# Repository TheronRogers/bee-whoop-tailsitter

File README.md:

# Bee Whoop Tailsitter

Affordable dual-motor, dual-elevon tailsitter platform (Bee). Prototype path: learn custom PCB + printable airframe, then flyable AIO.

## Layout

- `cad/` — Rad CAD / VibeCAD airframe (BeeWhoopTailsitter)
- `electronics/` — Bee Core bring-up board (RP2350 KiCad design)

## Airframe (v0)

| Spec | Value |
|------|--------|
| Span | 120 mm |
| Mean chord | 48 mm (root 52 / tip 44) |
| Area | ~5760 mm² |
| Motors | Y ±30 mm, 40 mm prop discs |
| Elevons | 15 mm chord, 8 mm root gap |
| AIO tray | 32×36×8 mm @ ~33% MAC |
| Battery cue | 1S near LE |
| Servos | 2× micro ~9×12×22 |
| Materials | PLA + Air/LW-PLA; PETG/CF hardpoints |
| AUW / T/W | ~100 g / target 2.0 — verify 0802/1S thrust |

No tilt rotor, swashplate, or collective. Fixed motors + elevons + differential thrust.

## Electronics (Bee Core bring-up)

- RP2350A + QSPI flash + USB-C + SWD
- BMI270 IMU (SPI)
- 1× EFM8BB21 ESC channel, Bluejay **Layout O**, EFM8 on VBAT (1S)
- 1× servo PWM + companion header
- KiCad 9 project under `electronics/bee-core-bringup/bee-core-v01/`
- Schematic ERC clean; **PCB layout not fab-ready** (routing paused for manual finish)
- Bring-up board outline ~80×60 mm; flight target 32×36 mm

See `electronics/bee-core-bringup/` docs (`DESIGN.md`, `ESC-TOPOLOGY-DECISION.md`, `PCB-STATUS.md`).

## Status

**Paused** (see `PAUSED.md`). Notes preserved under `notes/` so the trail survives the pause.

PCB routing still awaits manual / alternate tooling when resumed.

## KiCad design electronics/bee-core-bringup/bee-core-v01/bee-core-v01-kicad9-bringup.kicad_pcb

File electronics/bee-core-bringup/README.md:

# Bee Core — RP2350 bring-up board (v0.1)

Hardware foundation for grafting flight peripherals onto Raspberry Pi’s official
**RP2350A Minimal** KiCad design. Target: JLCPCB PCBA, qty 5, prefer 4-layer.

## Layout

| Path | Contents |
|------|----------|
| `DESIGN.md` | Purpose, block diagram, proof-order, fab posture, scope |
| `BOM-TARGETS.md` | Functional blocks + preferred LCSC candidates |
| `ESC-NOTES.md` | Single-channel whoop ESC topology (cited sources) |
| `NEXT-STEPS.md` | Immediate schematic graft plan |
| `vendor/rp2350-minimal/` | Untouched RPi Minimal KiCad zip extract |
| `vendor/RP2350A_Minimal_USBC/` | JLCPCB/LCSC-mapped fork (funvill) — reference only |
| `kicad/` | Pristine Minimal copy (reference; leave intact) |
| `bee-core-v01/` | **Working KiCad project** + graft sheets; see `SCHEMATIC-NOTES.md` |

## Sources

- Official Minimal: https://datasheets.raspberrypi.com/rp2350/Minimal-KiCAD.zip  
  → `RPI-RP2350A-MINIMAL_R4-S1` (RP2350A QFN-60)
- JLCPCB-mapped fork: https://github.com/funvill/RP2350A_Minimal_USBC
- Hardware design guide: https://datasheets.raspberrypi.com/rp2350/hardware-design-with-rp2350.pdf

## Tooling

| Tool | Version / method |
|------|------------------|
| KiCad | **9.0.2** (`sudo apt-get install -y kicad`, Debian package `9.0.2+dfsg-1`) |
| CLI | `kicad-cli` 9.0.2 (`kicad-cli version`) |
| GUI | `/usr/bin/kicad` (same package; needs display) |

Upstream Minimal sources are **KiCad 10**. Working schematic in `bee-core-v01/` was
downgraded to load in 9.0.2; PCB remains KiCad 10 until a newer KiCad is available.

## Locked v0.1 scope (summary)

RP2350A + QSPI flash + USB-C + SWD + BOOTSEL/RUN + 3V3 from USB; BMI270 or
ICM-42688 SPI IMU; 1× EFM8BB21 Bluejay ESC channel; 1× servo PWM + 5V BEC;
status LED; COMPANION 6-pin header (unpopulated).

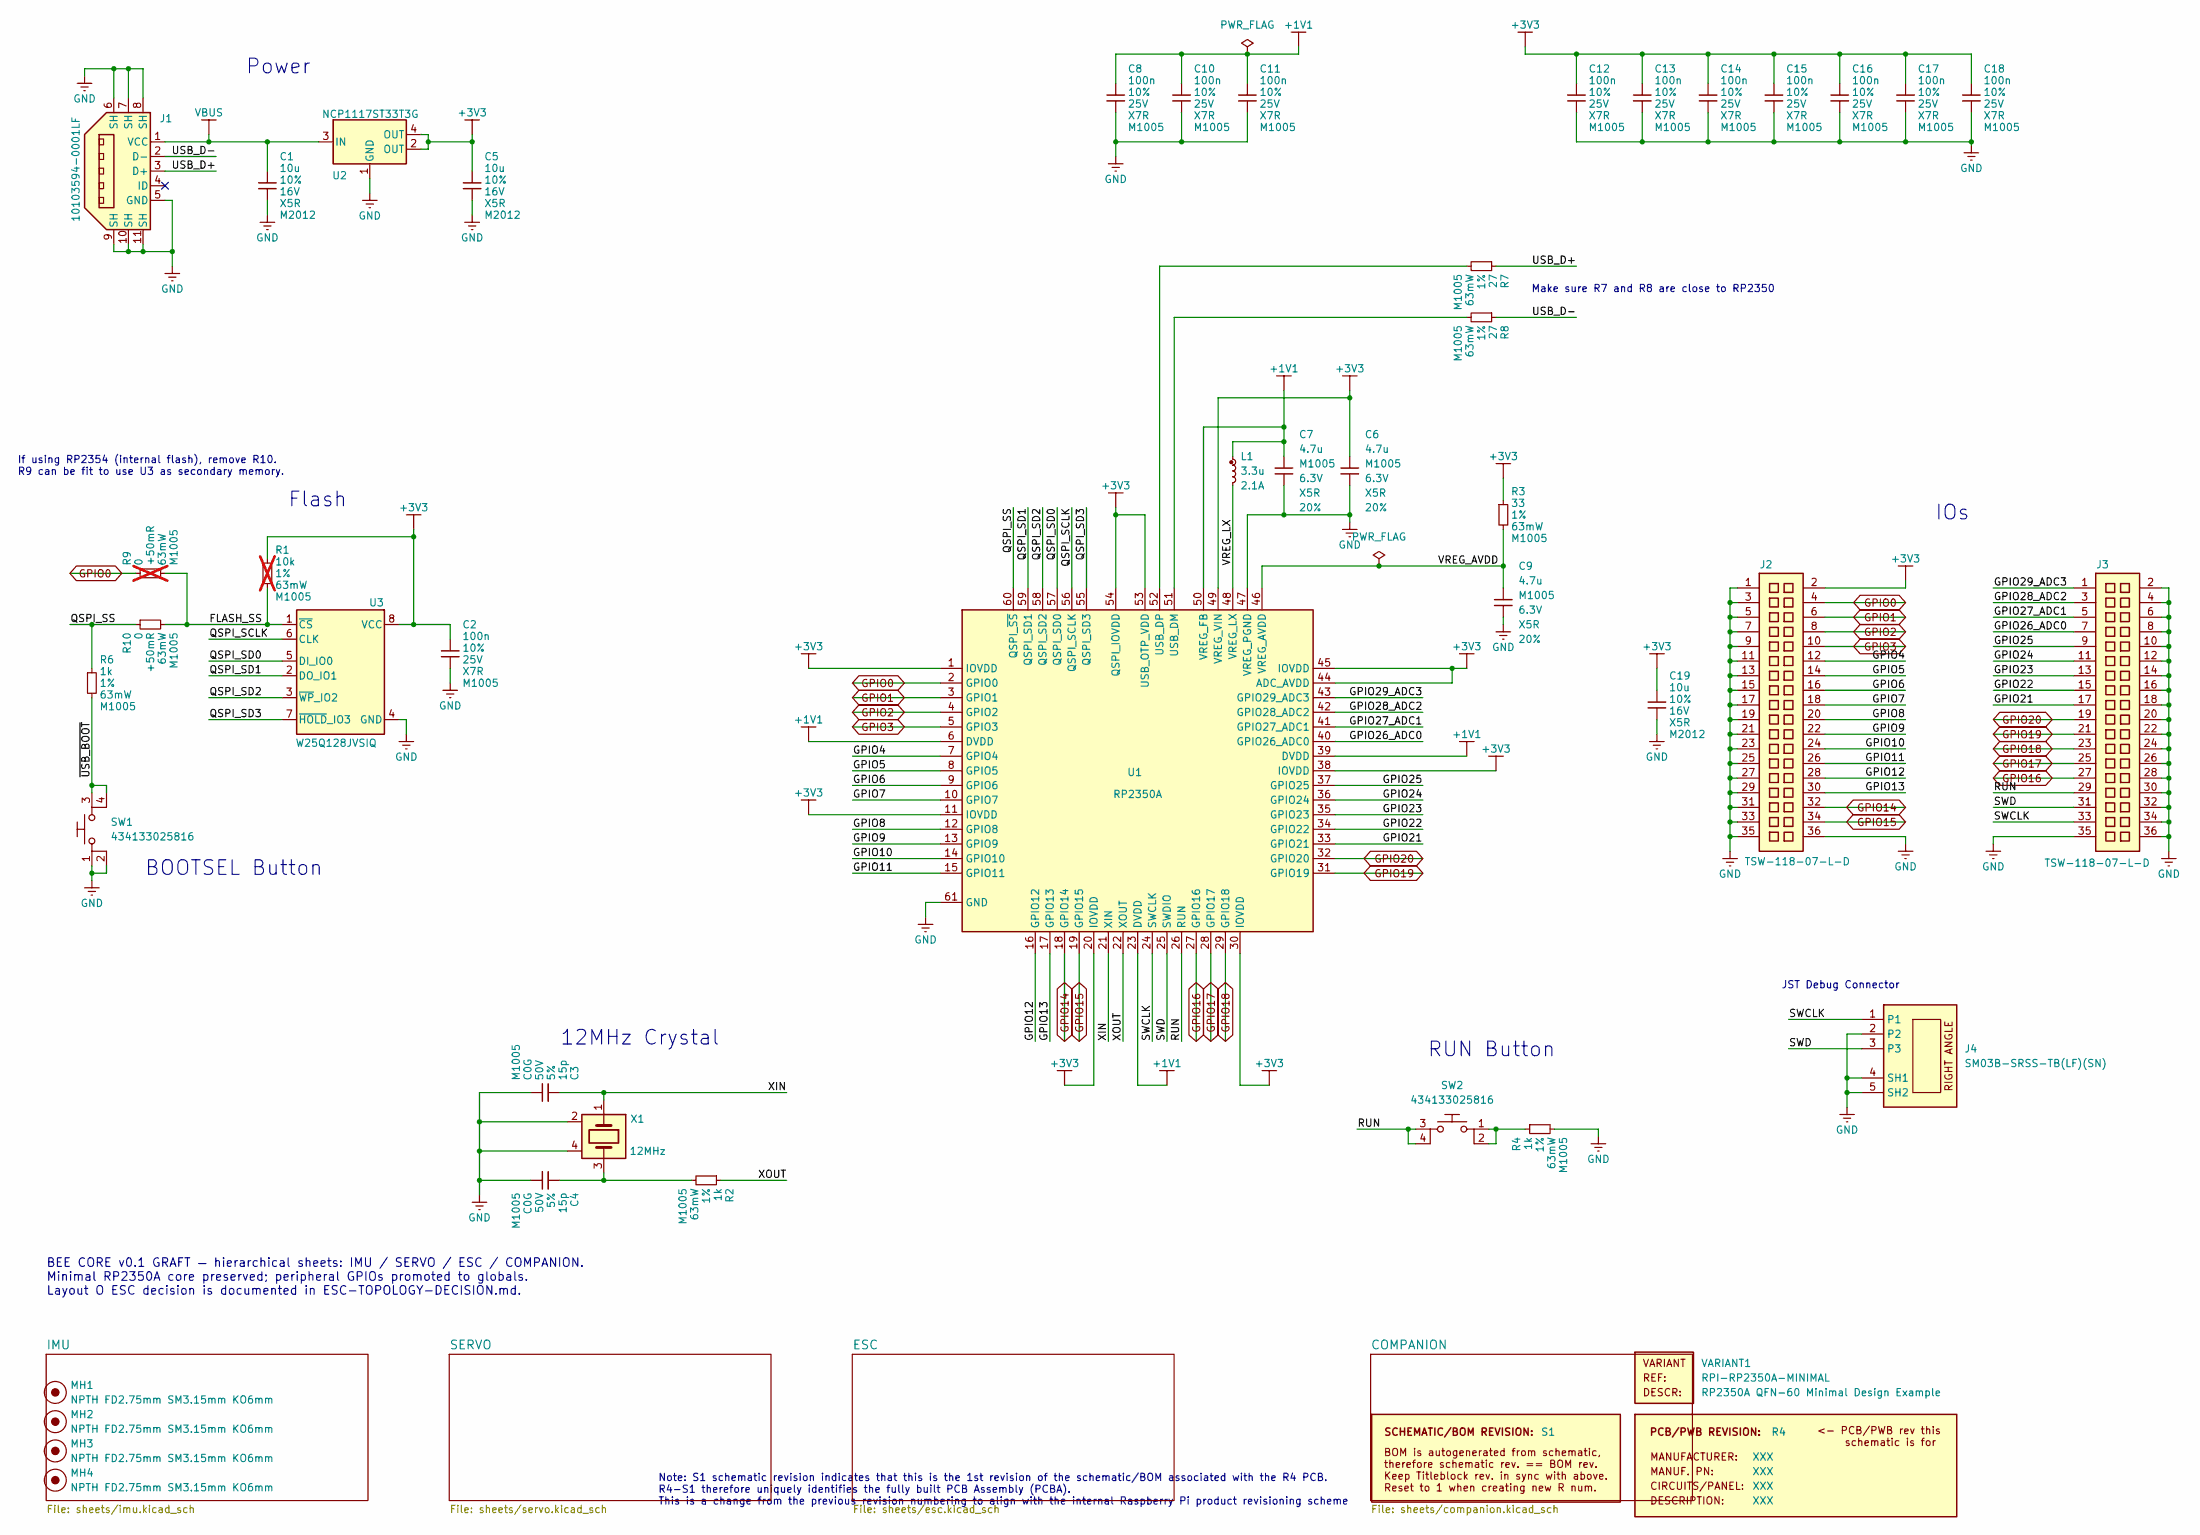
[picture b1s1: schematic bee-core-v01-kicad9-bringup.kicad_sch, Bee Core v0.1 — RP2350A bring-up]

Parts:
C1, C5, C19: 10u; C_0805_2012Metric; voltage 16V; tolerance 10%; part_uid RP-01GYSK-AVBE41
C2, C8, C10, C11, C12, C13, C14, C15, C16, C17, C18: 100n; C_0402_1005Metric; voltage 25V; tolerance 10%; part_uid RP-01BJ9Y-KRGF41
C3, C4: 15p; C_0402_1005Metric; voltage 50V; tolerance 5%; part_uid RP-01C89W-LLY9XV
C6, C7, C9: 4.7u; C_0402_1005Metric; voltage 6.3V; tolerance 20%; part_uid RP-019A1P-0C2GHY
J1: 10103594-0001LF; PinHeader_2x06_P2.54mm_Vertical; part_uid RP-019A1P-1JAX7V
J2, J3: TSW-118-07-L-D; PinHeader_2x18_P2.54mm_Horizontal; part_uid RP-01JWH2-G371Y4
J4: SM03B-SRSS-TB(LF)(SN); PinHeader_1x05_P2.54mm_Vertical; part_uid RP-01EKJ1-8V9SV1
L1: 3.3u; L_Cenker_CKCS201610; tolerance 20%; part_uid RP-01GY5D-2VC7WP
MH1, MH2, MH3, MH4: NPTH FD2.75mm SM3.15mm KO6mm; MountingHole_2.7mm_M2.5; part_uid RP-01HF5R-LCTEJS
PCB1: R4; manufacturer_pn XXX
R1: 10k; R_0402_1005Metric; tolerance 1%; voltage 50V; part_uid RP-019A1P-53DHSX; not fitted
R2, R4, R6: 1k; R_0402_1005Metric; tolerance 1%; voltage 50V; part_uid RP-019A1P-4Z6ZWY
R3: 33; R_0402_1005Metric; tolerance 1%; voltage 50V; part_uid RP-019A1P-58PW9L
R7, R8: 27; R_0402_1005Metric; tolerance 1%; voltage 50V; part_uid RP-01C89V-LTEYC4
R9: 0; R_0402_1005Metric; tolerance +50mR; voltage 50V; part_uid RP-019A1P-4Y4V63; not fitted
R10: 0; R_0402_1005Metric; tolerance +50mR; voltage 50V; part_uid RP-019A1P-4Y4V63
SBREV1: S1
SW1, SW2: 434133025816; PinHeader_1x04_P2.54mm_Vertical; part_uid RP-01H0MT-6E9H8F
U1: RP2350A; QFN-60-1EP_7x7mm_P0.4mm_EP3.4x3.4mm_ThermalVias; part_uid RP-01HA9H-9K5E8T
U2: NCP1117ST33T3G; SOIC-8_3.9x4.9mm_P1.27mm; voltage 3.3V; part_uid RP-01JWD9-7JRX6J
U3: W25Q128JVSIQ; SOIC-8_3.9x4.9mm_P1.27mm; voltage 2.7-3.6V; part_uid RP-01JWD4-F1H4N9
VARIANT1: RPI-RP2350A-MINIMAL
X1: 12MHz; Crystal_SMD_3225-4Pin_3.2x2.5mm; tolerance 30ppm; part_uid RP-01G8X7-GS352B

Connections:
+1V1: C7.1, C8.1, C10.1, C11.1, L1.1, U1.6 (DVDD), U1.23 (DVDD), U1.39 (DVDD), U1.50 (VREG_FB)
+3V3: C2.1, C5.1, C6.1, C12.1, C13.1, C14.1, C15.1, C16.1, C17.1, C18.1, C19.1, J2.2, R1.1, R3.1, U1.1 (IOVDD), U1.11 (IOVDD), U1.20 (IOVDD), U1.30 (IOVDD), U1.38 (IOVDD), U1.44 (ADC_AVDD), U1.45 (IOVDD), U1.49 (VREG_VIN), U1.53 (USB_OTP_VDD), U1.54 (QSPI_IOVDD), U2.2 (OUT), U2.4 (OUT), U3.8 (VCC); also elsewhere on the board
/FLASH_SS: R1.2, R9.2, R10.2, U3.1 (~CS)
/GPIO4: J2.12, U1.7 (GPIO4)
/GPIO5: J2.14, U1.8 (GPIO5)
/GPIO6: J2.16, U1.9 (GPIO6)
/GPIO7: J2.18, U1.10 (GPIO7)
/GPIO8: J2.20, U1.12 (GPIO8)
/GPIO9: J2.22, U1.13 (GPIO9)
/GPIO10: J2.24, U1.14 (GPIO10)
/GPIO11: J2.26, U1.15 (GPIO11)
/GPIO12: J2.28, U1.16 (GPIO12)
/GPIO13: J2.30, U1.17 (GPIO13)
/GPIO21: J3.17, U1.33 (GPIO21)
/GPIO22: J3.15, U1.34 (GPIO22)
/GPIO23: J3.13, U1.35 (GPIO23)
/GPIO24: J3.11, U1.36 (GPIO24)
/GPIO25: J3.9, U1.37 (GPIO25)
/GPIO26_ADC0: J3.7, U1.40 (GPIO26_ADC0)
/GPIO27_ADC1: J3.5, U1.41 (GPIO27_ADC1)
/GPIO28_ADC2: J3.3, U1.42 (GPIO28_ADC2)
/GPIO29_ADC3: J3.1, U1.43 (GPIO29_ADC3)
/QSPI_SCLK: U1.56 (QSPI_SCLK), U3.6 (CLK)
/QSPI_SD0: U1.57 (QSPI_SD0), U3.5 (DI_IO0)
/QSPI_SD1: U1.59 (QSPI_SD1), U3.2 (DO_IO1)
/QSPI_SD2: U1.58 (QSPI_SD2), U3.3 (~WP_IO2)
/QSPI_SD3: U1.55 (QSPI_SD3), U3.7 (~HOLD_IO3)
/QSPI_SS: R6.1, R10.1, U1.60 (QSPI_~SS)
/RUN: J3.29, SW2.3, SW2.4, U1.26 (RUN)
/SWCLK: J3.33, J4.1, U1.24 (SWCLK)
/SWD: J3.31, J4.3, U1.25 (SWDIO)
/USB_D+: J1.3 (D+), R7.1
/USB_D-: J1.2 (D-), R8.1
/VREG_AVDD: C9.1, R3.2, U1.46 (VREG_AVDD)
/VREG_LX: L1.2, U1.48 (VREG_LX)
/XIN: C3.1, U1.21 (XIN), X1.1
/XOUT: R2.1, U1.22 (XOUT)
/~USB_BOOT: R6.2, SW1.3, SW1.4
GND: C1.2, C2.2, C3.2, C4.2, C5.2, C6.2, C7.2, C8.2, C9.2, C10.2, C11.2, C12.2, C13.2, C14.2, C15.2, C16.2, C17.2, C18.2, C19.2, J1.5 (GND), J1.6 (SH), J1.7 (SH), J1.8 (SH), J1.9 (SH), J1.10 (SH), J1.11 (SH), J2.1, J2.3, J2.5, J2.7, J2.9, J2.11, J2.13, J2.15, J2.17, J2.19, J2.21, J2.23, J2.25, J2.27, J2.29, J2.31, J2.33, J2.35, J2.36, J3.2, J3.4, J3.6, J3.8, J3.10, J3.12, J3.14, J3.16, J3.18, J3.20, J3.22, J3.24, J3.26, J3.28, J3.30, J3.32, J3.34, J3.35, J3.36, J4.2, J4.4 (SH1), J4.5 (SH2), R4.2, SW1.1, SW1.2, U1.47 (VREG_PGND), U1.61 (GND), U2.1 (GND), U3.4 (GND), X1.2, X1.4; also elsewhere on the board
GPIO0: J2.4, R9.1, U1.2 (GPIO0); also elsewhere on the board
GPIO1: J2.6, U1.3 (GPIO1)
GPIO2: J2.8, U1.4 (GPIO2); also elsewhere on the board
GPIO3: J2.10, U1.5 (GPIO3); also elsewhere on the board
GPIO14: J2.32, U1.18 (GPIO14); also elsewhere on the board
GPIO15: J2.34, U1.19 (GPIO15); also elsewhere on the board
GPIO16: J3.27, U1.27 (GPIO16); also elsewhere on the board
GPIO17: J3.25, U1.28 (GPIO17); also elsewhere on the board
GPIO18: J3.23, U1.29 (GPIO18); also elsewhere on the board
GPIO19: J3.21, U1.31 (GPIO19); also elsewhere on the board
GPIO20: J3.19, U1.32 (GPIO20); also elsewhere on the board
unnamed: C4.1, R2.2, X1.3
unnamed: R4.1, SW2.1, SW2.2
unnamed: R8.2, U1.51 (USB_DM)
unnamed: R7.2, U1.52 (USB_DP)
VBUS: C1.1, J1.1 (VCC), U2.3 (IN)

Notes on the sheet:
JST Debug Connector
IOs
RUN Button
BOOTSEL Button
If using RP2354 (internal flash), remove R10. R9 can be fit to use U3 as secondary memory.
BEE CORE v0.1 GRAFT — hierarchical sheets: IMU / SERVO / ESC / COMPANION. Minimal RP2350A core preserved; peripheral GPIOs promoted to globals. Layout O ESC decision is documented in ESC-TOPOLOGY-DECISION.md.
Flash
Note: S1 schematic revision indicates that this is the 1st revision of the schematic/BOM associated with the R4 PCB. R4-S1 therefore uniquely identifies the fully built PCB Assembly (PCBA). This is a change from the previous revision numbering to align with the internal Raspberry Pi product revisio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
Make sure R7 and R8 are close to RP2350
12MHz Crystal
Power

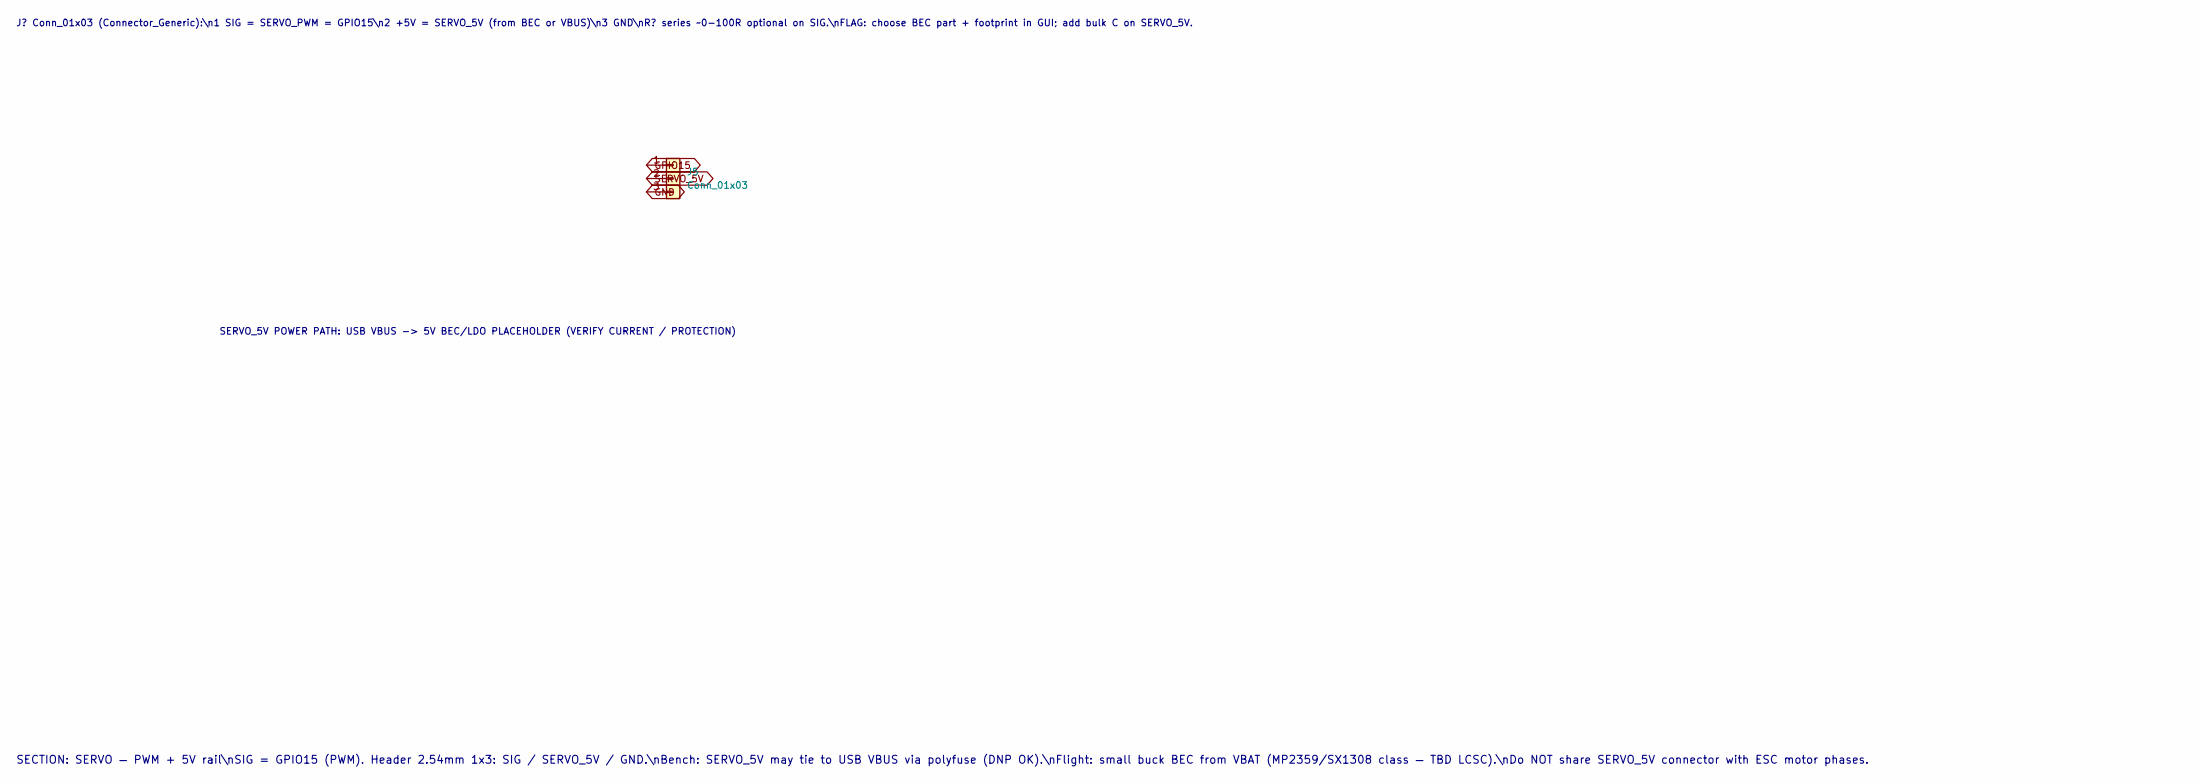
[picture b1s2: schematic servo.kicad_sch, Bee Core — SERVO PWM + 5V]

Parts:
J5: Conn_01x03; PinHeader_1x03_P2.54mm_Vertical

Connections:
GND: J5.3; also elsewhere on the board
GPIO15: J5.1; also elsewhere on the board
SERVO_5V: J5.2

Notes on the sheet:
J? Conn_01x03 (Connector_Generic):\n1 SIG = SERVO_PWM = GPIO15\n2 +5V = SERVO_5V (from BEC or VBUS)\n3 GND\nR? series ~0-100R optional on SIG.\nFLAG: choose BEC part + footprint in GUI; add bulk C on SERVO_5V.
SERVO_5V POWER PATH: USB VBUS -> 5V BEC/LDO PLACEHOLDER (VERIFY CURRENT / PROTECTION)
SECTION: SERVO — PWM + 5V rail\nSIG = GPIO15 (PWM). Header 2.54mm 1x3: SIG / SERVO_5V / GND.\nBench: SERVO_5V may tie to USB VBUS via polyfuse (DNP OK).\nFlight: small buck BEC from VBAT (MP2359/SX1308 class — TBD LCSC).\nDo NOT share SERVO_5V connector with ESC motor phases.

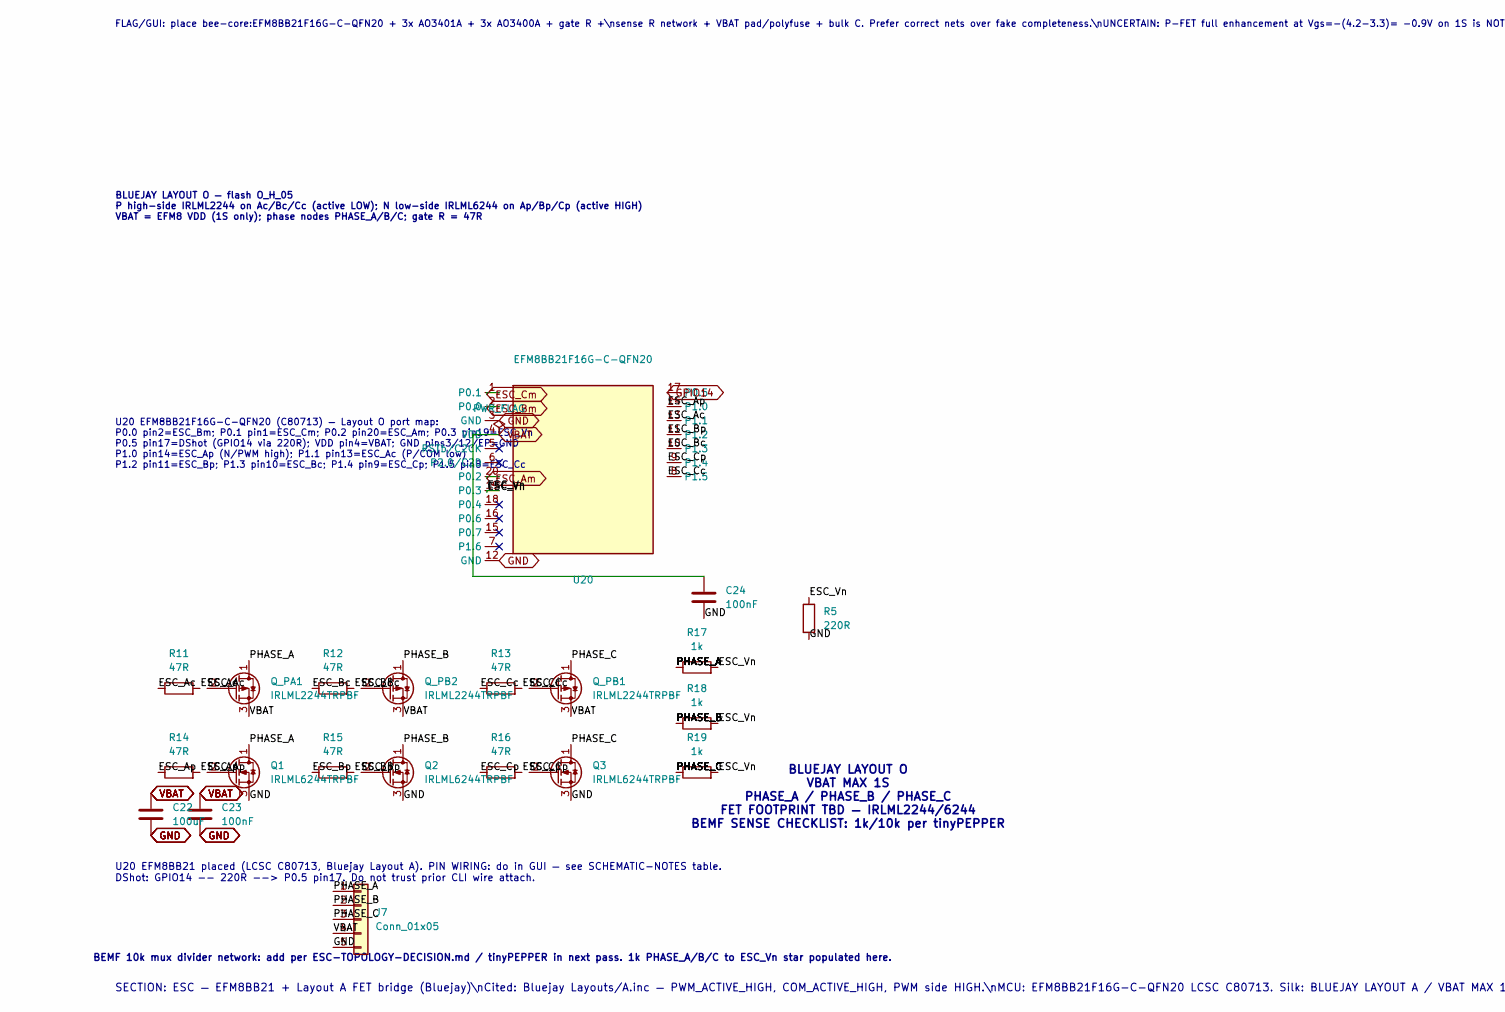
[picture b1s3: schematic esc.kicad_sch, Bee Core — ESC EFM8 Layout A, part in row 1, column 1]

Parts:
C22: 100uF; C_0805_2012Metric_Pad1.18x1.45mm_HandSolder
C23, C24: 100nF; C_0402_1005Metric
J7: Conn_01x05; PinHeader_1x05_P2.54mm_Vertical
Q1, Q2, Q3: IRLML6244TRPBF; SOT-23-3
Q_PA1: IRLML2244TRPBF; SOT-23-3
Q_PB1, Q_PB2: IRLML2244TRPBF; SOT-23-3
R5: 220R; R_0402_1005Metric_Pad0.72x0.64mm_HandSolder
R11, R12, R13, R14, R15, R16: 47R; R_0402_1005Metric_Pad0.72x0.64mm_HandSolder
R17, R18, R19: 1k; R_0402_1005Metric_Pad0.72x0.64mm_HandSolder
U20: EFM8BB21F16G-C-QFN20; SiliconLabs_QFN-20-1EP_3x3mm_P0.5mm_EP1.8x1.8mm; LCSC C80713

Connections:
/ESC/ESC_Ac: Q_PA1.2 (G), R11.1, R11.2, U20.13 (P1.1)
/ESC/ESC_Ap: Q1.2 (G), R14.1, R14.2, U20.14 (P1.0)
/ESC/ESC_Bc: Q_PB2.2 (G), R12.1, R12.2, U20.10 (P1.3)
/ESC/ESC_Bp: Q2.2 (G), R15.1, R15.2, U20.11 (P1.2)
/ESC/ESC_Cc: Q_PB1.2 (G), R13.1, R13.2, U20.8 (P1.5)
/ESC/ESC_Cp: Q3.2 (G), R16.1, R16.2, U20.9 (P1.4)
/ESC/ESC_Vn: R5.1, R17.2, R18.2, R19.2, U20.19 (P0.3)
/ESC/PHASE_A: J7.1, Q1.1 (D), Q_PA1.1 (D), R17.1
/ESC/PHASE_B: J7.2, Q2.1 (D), Q_PB2.1 (D), R18.1
/ESC/PHASE_C: J7.3, Q3.1 (D), Q_PB1.1 (D), R19.1
ESC_Am: U20.20 (P0.2)
ESC_Bm: U20.2 (P0.0)
ESC_Cm: U20.1 (P0.1)
GND: C22.2, C23.2, C24.2, J7.5, Q1.3 (S), Q2.3 (S), Q3.3 (S), R5.2, U20.3 (GND), U20.12 (GND); also elsewhere on the board
GPIO14: U20.17 (P0.5); also elsewhere on the board
VBAT: C22.1, C23.1, C24.1, J7.4, Q_PA1.3 (S), Q_PB1.3 (S), Q_PB2.3 (S), U20.4 (VDD)

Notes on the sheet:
U20 EFM8BB21 placed (LCSC C80713, Bluejay Layout A). PIN WIRING: do in GUI — see SCHEMATIC-NOTES table. DShot: GPIO14 -- 220R --> P0.5 pin17. Do not trust prior CLI wire attach.
BLUEJAY LAYOUT O VBAT MAX 1S PHASE_A / PHASE_B / PHASE_C FET FOOTPRINT TBD — IRLML2244/6244 BEMF SENSE CHECKLIST: 1k/10k per tinyPEPPER
BLUEJAY LAYOUT O — flash O_H_05 P high-side IRLML2244 on Ac/Bc/Cc (active LOW); N low-side IRLML6244 on Ap/Bp/Cp (active HIGH) VBAT = EFM8 VDD (1S only); phase nodes PHASE_A/B/C; gate R = 47R
U20 EFM8BB21F16G-C-QFN20 (C80713) — Layout O port map: P0.0 pin2=ESC_Bm; P0.1 pin1=ESC_Cm; P0.2 pin20=ESC_Am; P0.3 pin19=ESC_Vn P0.5 pin17=DShot (GPIO14 via 220R); VDD pin4=VBAT; GND pins3/12/EP=GND P1.0 pin14=ESC_Ap (N/PWM high); P1.1 pin13=ESC_Ac (P/COM low) P1.2 pin11=ESC_Bp; P1.3 pin10=ESC_Bc; 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
FLAG/GUI: place bee-core:EFM8BB21F16G-C-QFN20 + 3x AO3401A + 3x AO3400A + gate R +\nsense R network + VBAT pad/polyfuse + bulk C. Prefer correct nets over fake completeness.\nUNCERTAIN: P-FET full enhancement at Vgs=-(4.2-3.3)= -0.9V on 1S is NOT enough —\nwhoop designs often gate P-FETs from VBAT-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
BEMF 10k mux divider network: add per ESC-TOPOLOGY-DECISION.md / tinyPEPPER in next pass. 1k PHASE_A/B/C to ESC_Vn star populated here.
SECTION: ESC — EFM8BB21 + Layout A FET bridge (Bluejay)\nCited: Bluejay Layouts/A.inc — PWM_ACTIVE_HIGH, COM_ACTIVE_HIGH, PWM side HIGH.\nMCU: EFM8BB21F16G-C-QFN20 LCSC C80713. Silk: BLUEJAY LAYOUT A / VBAT MAX 1S.\nDShot: GPIO14 -- Rseries 100-330R --> EFM8 P0.5 (pin 17).\n1S direct-drive P+N whoo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

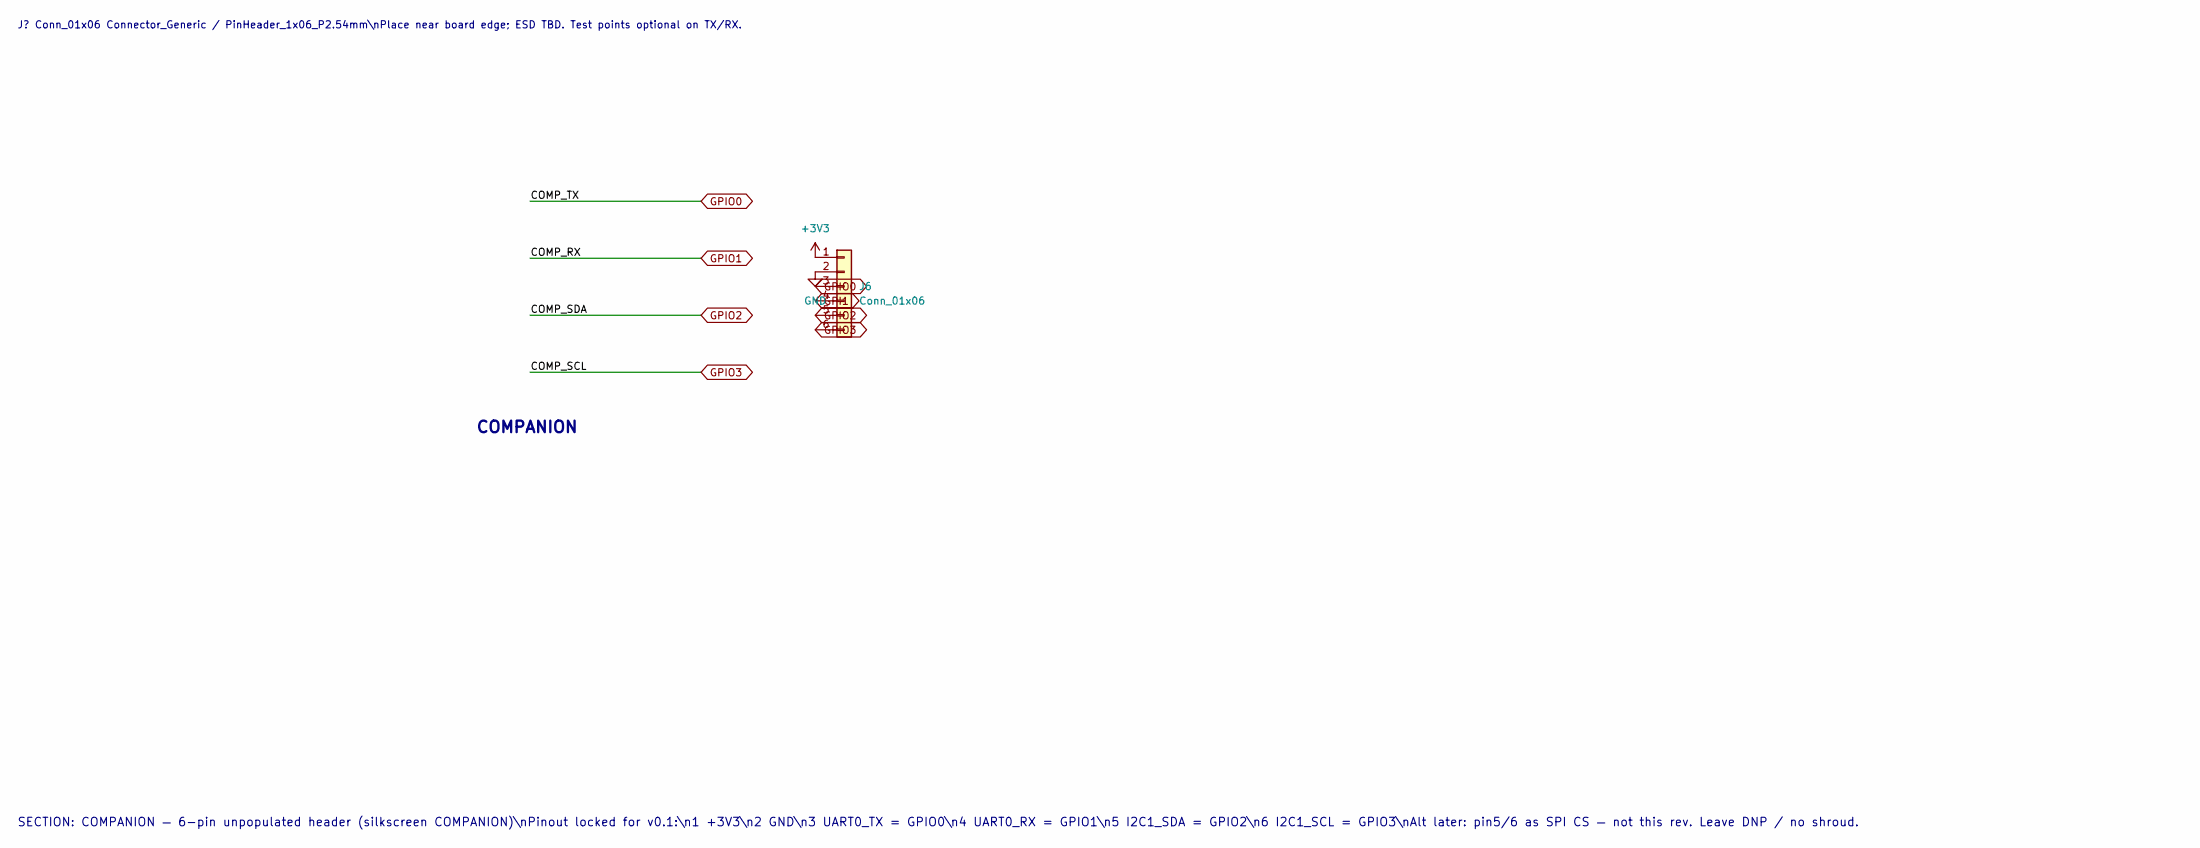
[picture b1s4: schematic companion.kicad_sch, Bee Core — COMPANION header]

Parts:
J6: Conn_01x06; PinHeader_1x06_P2.54mm_Vertical

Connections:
+3V3: J6.1; also elsewhere on the board
GND: J6.2; also elsewhere on the board
GPI1: J6.4
GPIO0: J6.3; also elsewhere on the board
GPIO2: J6.5; also elsewhere on the board
GPIO3: J6.6; also elsewhere on the board

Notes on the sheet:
COMPANION
SECTION: COMPANION — 6-pin unpopulated header (silkscreen COMPANION)\nPinout locked for v0.1:\n1 +3V3\n2 GND\n3 UART0_TX = GPIO0\n4 UART0_RX = GPIO1\n5 I2C1_SDA = GPIO2\n6 I2C1_SCL = GPIO3\nAlt later: pin5/6 as SPI CS — not this rev. Leave DNP / no shroud.
J? Conn_01x06 Connector_Generic / PinHeader_1x06_P2.54mm\nPlace near board edge; ESD TBD. Test points optional on TX/RX.

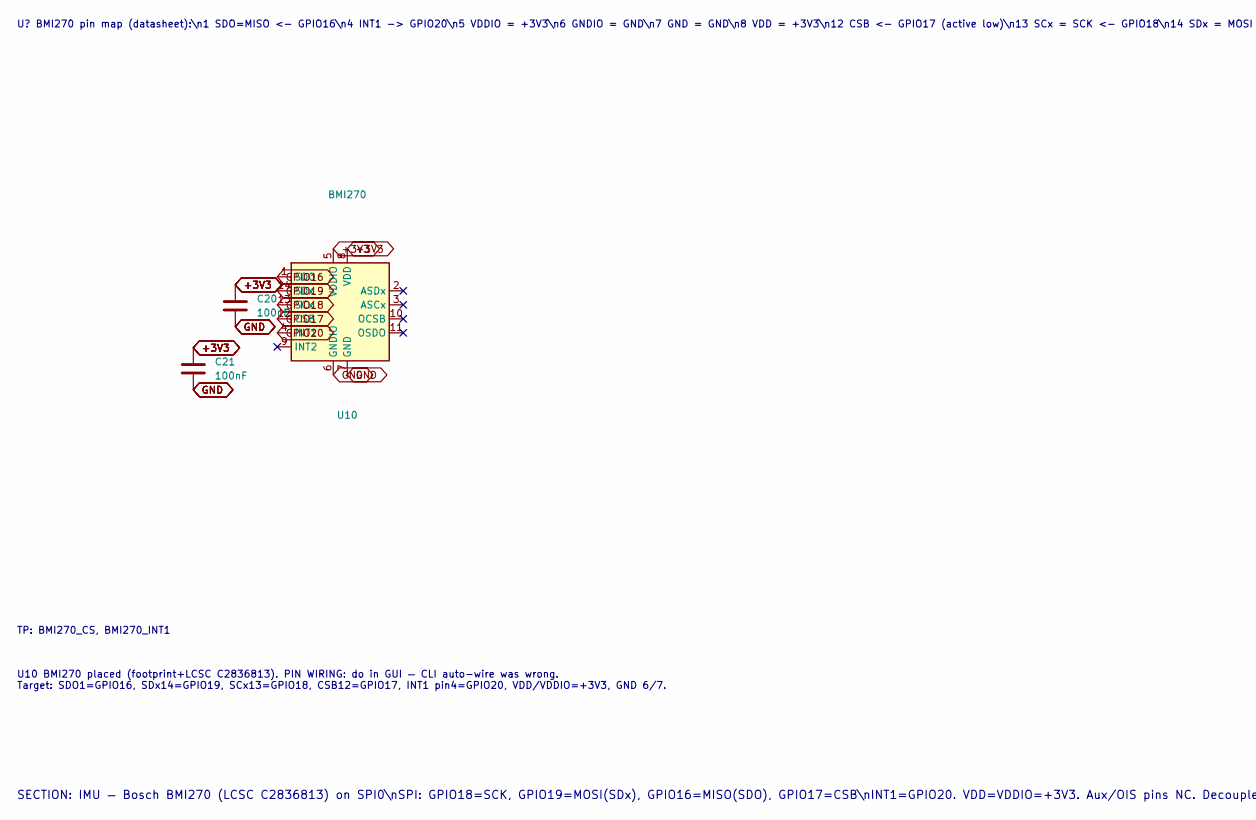
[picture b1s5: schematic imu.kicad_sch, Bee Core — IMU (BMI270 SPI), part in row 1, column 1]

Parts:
C20, C21: 100nF; C_0402_1005Metric
U10: BMI270; Bosch_LGA-14_3x2.5mm_P0.5mm; LCSC C2836813

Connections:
+3V3: C20.1, C21.1, U10.5 (VDDIO), U10.8 (VDD); also elsewhere on the board
GND: C20.2, C21.2, U10.6 (GNDIO), U10.7 (GND); also elsewhere on the board
GPIO16: U10.1 (SDO); also elsewhere on the board
GPIO17: U10.12 (CSB); also elsewhere on the board
GPIO18: U10.13 (SCx); also elsewhere on the board
GPIO19: U10.14 (SDx); also elsewhere on the board
GPIO20: U10.4 (INT1); also elsewhere on the board

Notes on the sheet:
U10 BMI270 placed (footprint+LCSC C2836813). PIN WIRING: do in GUI — CLI auto-wire was wrong. Target: SDO1=GPIO16, SDx14=GPIO19, SCx13=GPIO18, CSB12=GPIO17, INT1 pin4=GPIO20, VDD/VDDIO=+3V3, GND 6/7.
SECTION: IMU — Bosch BMI270 (LCSC C2836813) on SPI0\nSPI: GPIO18=SCK, GPIO19=MOSI(SDx), GPIO16=MISO(SDO), GPIO17=CSB\nINT1=GPIO20. VDD=VDDIO=+3V3. Aux/OIS pins NC. Decouple 100n near VDD/VDDIO.\nFootprint: Package_LGA:Bosch_LGA-14_3x2.5mm_P0.5mm
TP: BMI270_CS, BMI270_INT1
U? BMI270 pin map (datasheet):\n1 SDO=MISO <- GPIO16\n4 INT1 -> GPIO20\n5 VDDIO = +3V3\n6 GNDIO = GND\n7 GND = GND\n8 VDD = +3V3\n12 CSB <- GPIO17 (active low)\n13 SCx = SCK <- GPIO18\n14 SDx = MOSI <- GPIO19\n2,3,9,10,11 NC (no aux/OIS on v0.1)\nPLACEHOLDER: drop bee-core:BMI270 symbol in GUI and 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

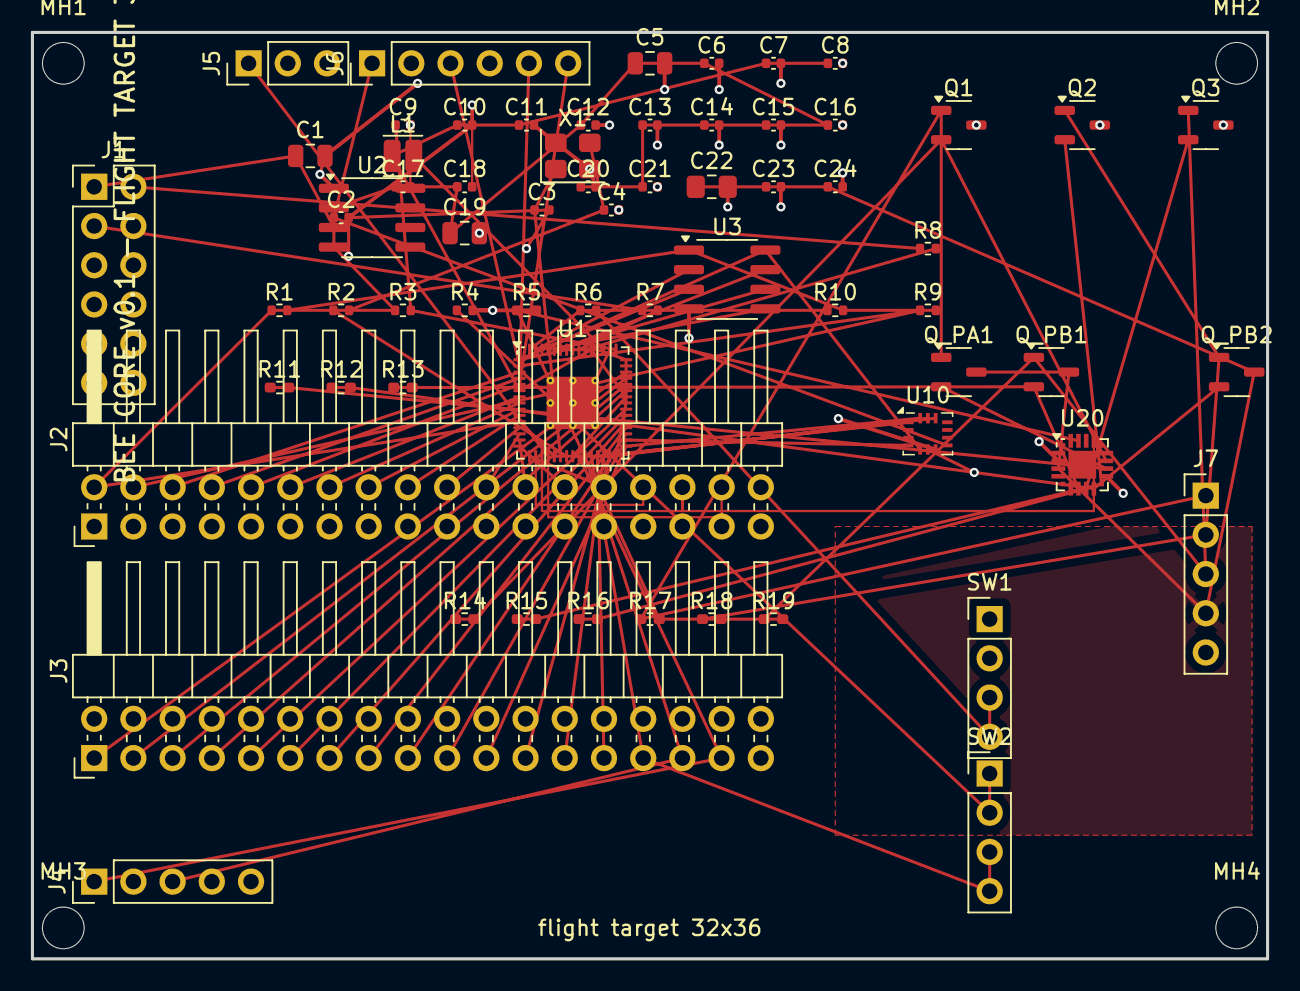
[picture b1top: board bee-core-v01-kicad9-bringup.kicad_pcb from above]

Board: 4 copper layers, 80.0 x 60.0 mm, 69 parts (0 on the bottom side), 66 nets.
